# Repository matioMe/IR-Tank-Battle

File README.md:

# IR-Tank-Battle
A little Infra-red game with tanks you can command with a smartphone.
## 3D files
Available here: https://www.thingiverse.com/thing:3679008
## Installation

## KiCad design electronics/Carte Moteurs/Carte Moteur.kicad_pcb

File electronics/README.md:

# Information on files

kicad version 4

for openning a kicad, you have to download all the files on your computer and openning the files.pro from kicad 4

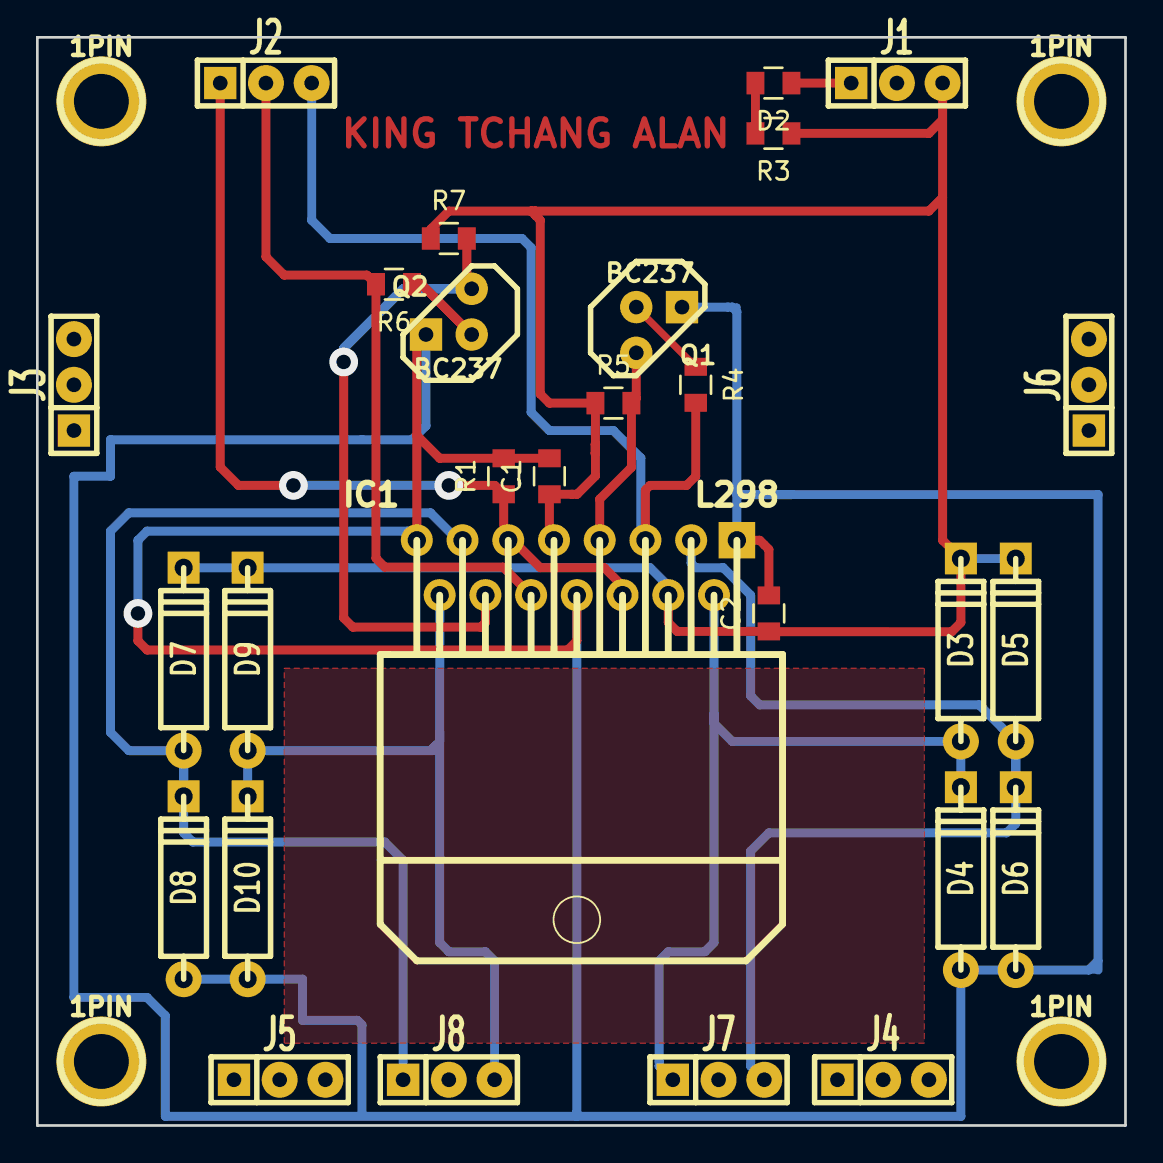
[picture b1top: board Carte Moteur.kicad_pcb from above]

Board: 2 copper layers, 60.5 x 60.5 mm, 32 parts (0 on the bottom side), 14 nets.

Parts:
1PIN, 1PIN#2, 1PIN#3, 1PIN#4: P***; Tom_TrouFixation
C1, C2: 100 µF; Tom_Capa_CMS_0805
D2: LED; Tom_Capa_CMS_0805
D3, D4, D5, D6, D7, D8, D9, D10: D; Tom_Diode
IC1: L298; Tom_L298_NH
J1, J2, J3, J4, J5, J6, J7, J8: Conn_01x03; Tom_SIL-3
Q1, Q2: BC237; Tom_TO92-EBC
R1, R4, R5, R6, R7: R; Tom_Capa_CMS_0805
R3: 470; Tom_Capa_CMS_0805

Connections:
//PWM1: IC1.7, Q1.C, R5.2
//PWM2: IC1.12, Q2.C, R7.2
/EN: IC1.6, IC1.11, J2.1, R1.1
/PWM1: IC1.5, J2.3, R4.2
/PWM2: IC1.10, J2.2, R6.2
GND: C1.2, C2.2, D2.1, D4.2, D6.2, D8.2, D10.2, IC1.1, IC1.8, IC1.15, J1.1, Q1.E, Q2.E, R1.2
unnamed: D2.2, R3.2
unnamed: D3.2, D4.1, IC1.2, J7.1
unnamed: D5.2, D6.1, IC1.3, J7.3
unnamed: D7.2, D8.1, IC1.13, J8.1
unnamed: D9.2, D10.1, IC1.14, J8.3
unnamed: Q1.B, R4.1
unnamed: Q2.B, R6.1
VCC: C1.1, C2.1, D3.1, D5.1, D7.1, D9.1, IC1.4, IC1.9, J1.3, R3.1, R5.1, R7.1

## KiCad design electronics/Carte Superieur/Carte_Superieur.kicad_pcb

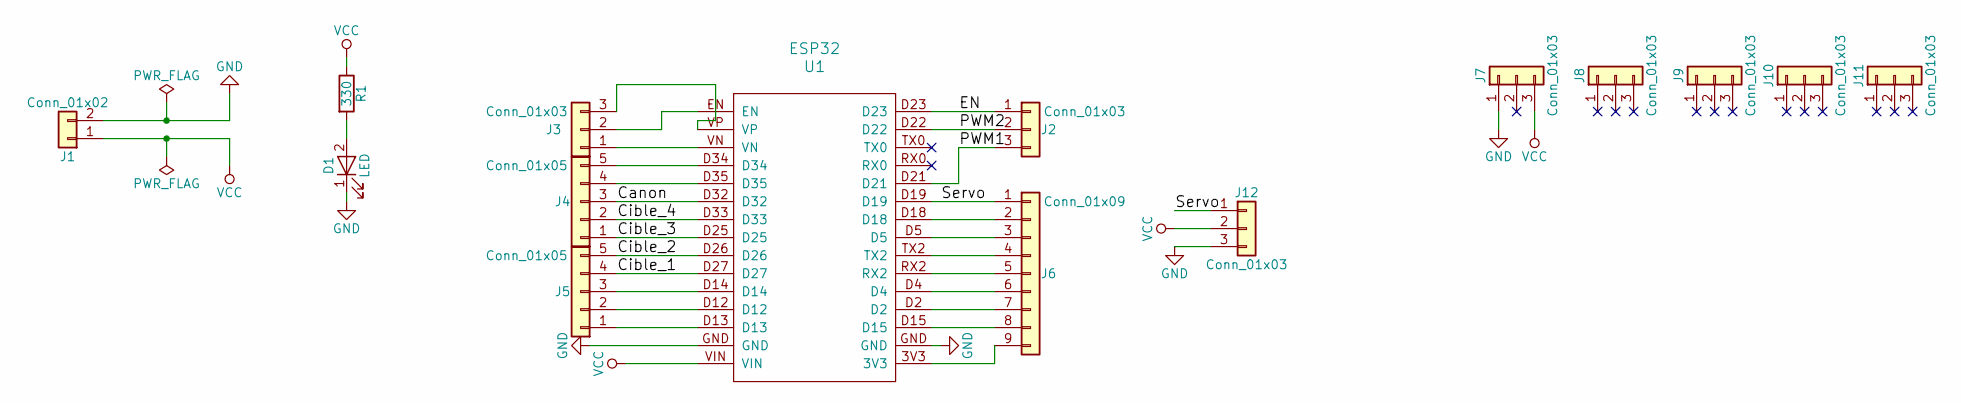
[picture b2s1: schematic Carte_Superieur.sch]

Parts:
D1: LED; Tom_Capa_CMS_0805
J1: Conn_01x02; Tom_bornier2
J2, J3, J7, J8, J9, J10, J11, J12: Conn_01x03; Tom_SIL-3
J4, J5: Conn_01x05; Tom_SIL-5
J6: Conn_01x09; Tom_SIL-9
R1: 330; Tom_Capa_CMS_0805
U1: ESP32

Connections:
/Canon: J4.3, U1.D32
/Cible_1: J5.4, U1.D27
/Cible_2: J5.5, U1.D26
/Cible_3: J4.1, U1.D25
/Cible_4: J4.2, U1.D33
/EN: J2.1, U1.D23
/PWM1: J2.3, U1.D21
/PWM2: J2.2, U1.D22
/Servo: J6.1, J12.1, U1.D19
GND: D1.1 (K), J1.2, J7.1, J12.3, U1.GND
unnamed: D1.2 (A), R1.2
unnamed: J3.1, U1.VN
unnamed: J3.2, U1.EN
unnamed: J3.3, U1.VP
unnamed: J4.4, U1.D35
unnamed: J4.5, U1.D34
unnamed: J5.1, U1.D13
unnamed: J5.2, U1.D12
unnamed: J5.3, U1.D14
unnamed: J6.2, U1.D18
unnamed: J6.3, U1.D5
unnamed: J6.4, U1.TX2
unnamed: J6.5, U1.RX2
unnamed: J6.6, U1.D4
unnamed: J6.7, U1.D2
unnamed: J6.8, U1.D15
unnamed: J6.9, U1.3V3
VCC: J1.1, J7.3, J12.2, R1.1, U1.VIN

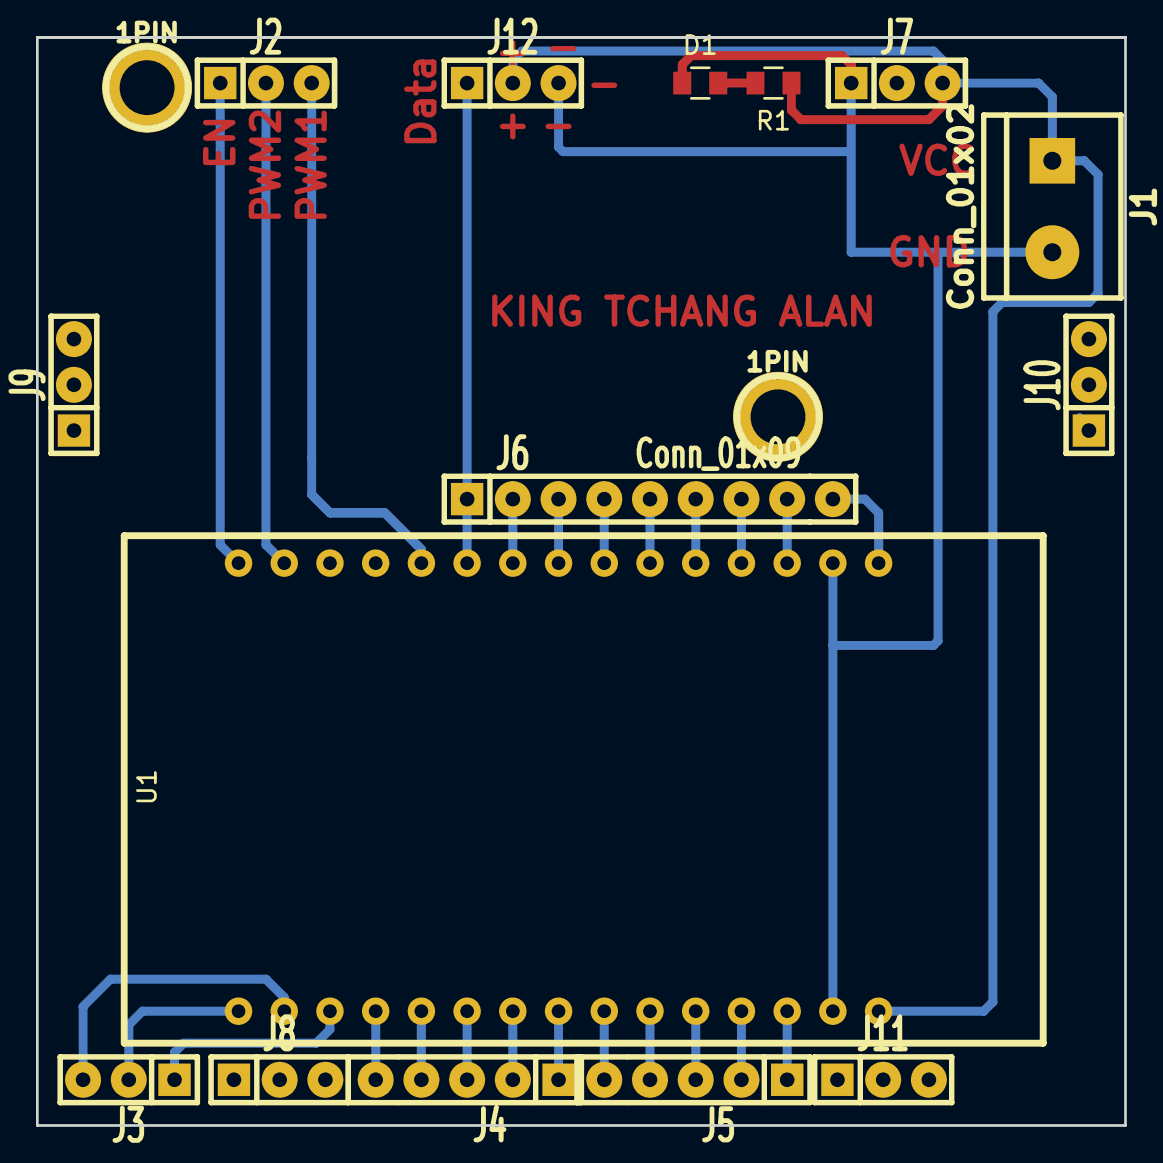
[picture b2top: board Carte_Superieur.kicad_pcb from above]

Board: 2 copper layers, 60.5 x 60.5 mm, 17 parts (0 on the bottom side), 28 nets.

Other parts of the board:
1PIN, 1PIN#2: P***; Tom_TrouFixation
